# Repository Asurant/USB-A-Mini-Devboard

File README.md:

# USB-A-Mini-Devboard
This is a small USB A Devboard I made. It uses a CH32V003J4M6 as the MCU. It was has 8 pins, 2 for the VBUS, 2 for the GND, and 4 for sensors and similar items. It is 34.5mm in length and 17mm in width.

## Hardware

[KiCanvas Link](https://kicanvas.org/?repo=https%3A%2F%2Fgithub.com%2FAsurant%2FUSB-A-Mini-Devboard%2Ftree%2Fmain%2Fsrc%2Fkicad)
### Schematic

### PCB

### Case

I personally hate it when 3D prints need outside items to make them work so I designed this case not to require screws but instead inbuilt pegs.

### Render

[Onshape Link](https://cad.onshape.com/documents/5c65439f048b848584ec4460/w/9e9735b3b4676a2554d27bed/e/21772a49cf2d0c4a67fcd84c?renderMode=0&uiState=6a110efd986242b2ed622441)

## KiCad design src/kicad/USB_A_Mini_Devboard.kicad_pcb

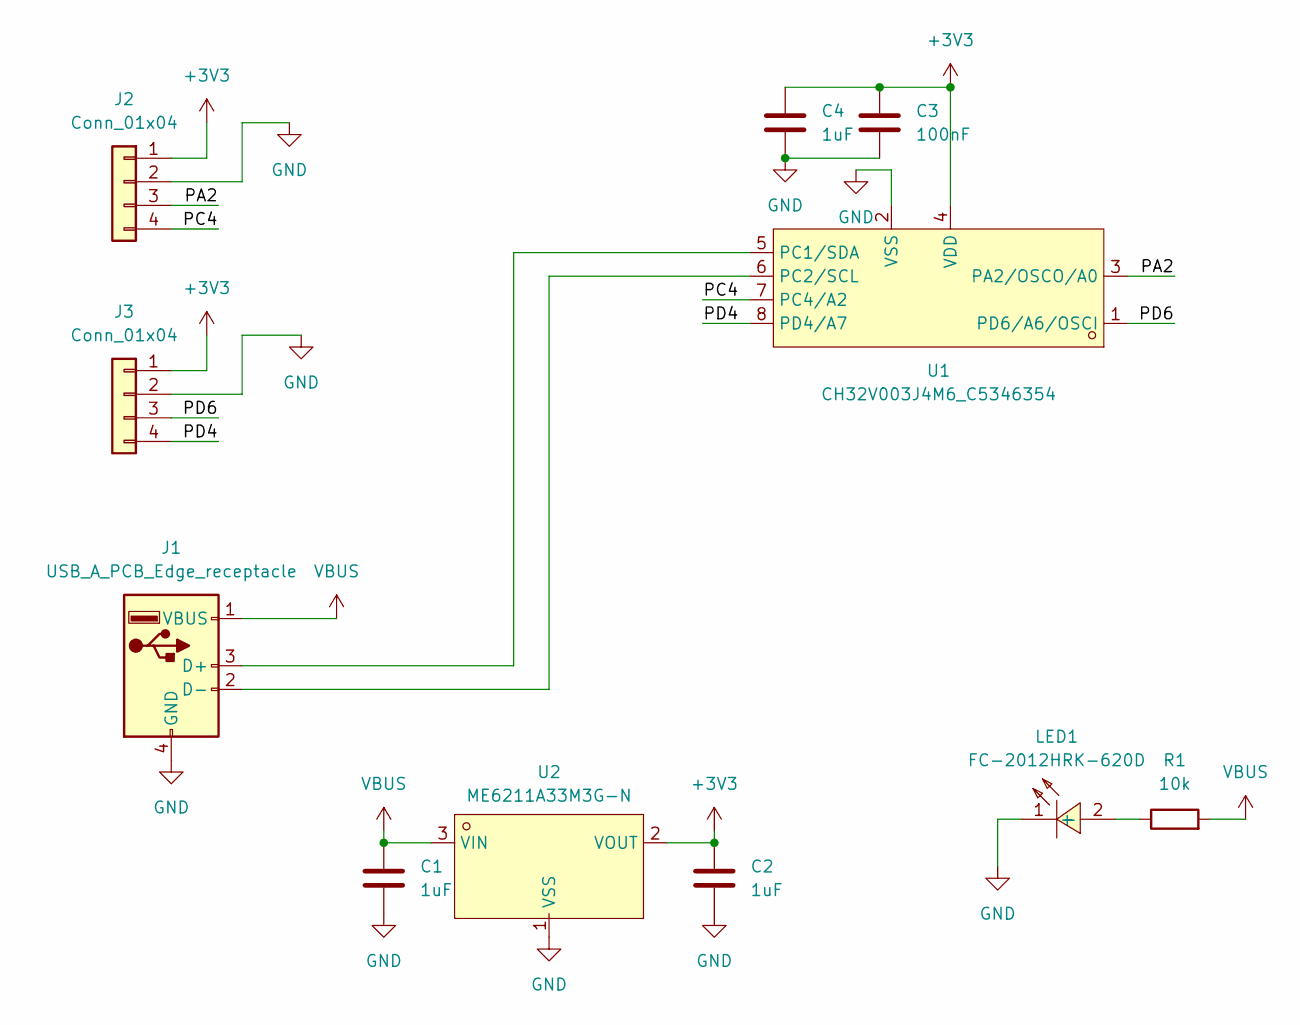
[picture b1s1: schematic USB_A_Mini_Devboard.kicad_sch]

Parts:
C1, C2, C4: 1uF; C_0603_1608Metric; LCSC Part C29936
C3: 100nF; C_0603_1608Metric; LCSC Part C1591
J1: USB_A_PCB_Edge_receptacle
J2, J3: Conn_01x04; PinHeader_1x04_P2.54mm_Vertical; LCSC Part C2691448
LED1: FC-2012HRK-620D; LED0805-RD; MPN NCD0805R1; LCSC Part C84256
R1: 10k; R_0603_1608Metric; LCSC Part C2930027
U1: CH32V003J4M6_C5346354; SOP-8_L4.9-W3.8-P1.27-LS6.0-BL; MPN CH32V003J4M6; LCSC Part C5346354
U2: ME6211A33M3G-N; SOT-23-3_L2.9-W1.6-P1.90-LS2.8-BR; MPN ME6211A33M3G-N; LCSC Part C168807

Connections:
+3V3: C2.1, C3.1, C4.1, J2.1, J3.1, U1.4 (VDD), U2.2 (VOUT)
/PA2: J2.3, U1.3 (PA2/OSCO/A0)
/PC4: J2.4, U1.7 (PC4/A2)
/PD4: J3.4, U1.8 (PD4/A7)
/PD6: J3.3, U1.1 (PD6/A6/OSCI)
GND: C1.2, C2.2, C3.2, C4.2, J1.4 (GND), J2.2, J3.2, LED1.1 (-), U1.2 (VSS), U2.1 (VSS)
unnamed: J1.3 (D+), U1.5 (PC1/SDA)
unnamed: J1.2 (D-), U1.6 (PC2/SCL)
unnamed: LED1.2 (+), R1.1
VBUS: C1.1, J1.1 (VBUS), R1.2, U2.3 (VIN)

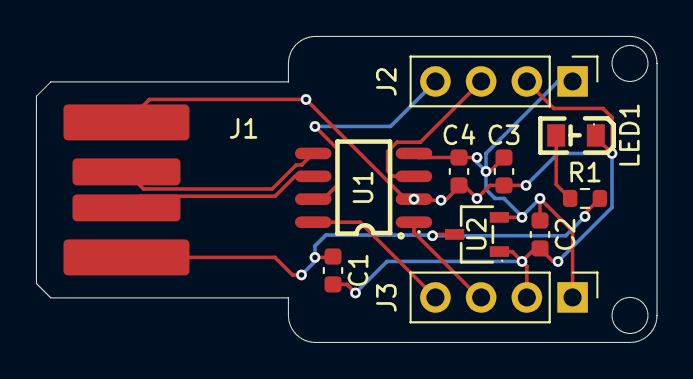
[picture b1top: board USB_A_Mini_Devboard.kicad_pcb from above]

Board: 2 copper layers, 34.5 x 17.0 mm, 11 parts (0 on the bottom side), 10 nets.

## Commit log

2026-05-19 Rename Screenshot 2026-05-19 121321.png to Image8
2026-05-19 Rename Image8 to Image8.png
2026-05-19 Rename Screenshot 2026-05-19 121354.png to Image9.png
2026-05-19 Rename Screenshot 2026-05-19 121423.png to Image10.png
2026-05-23 Rename src/kicad/USB_A_Mini_Devboard.step to src/USB_A_Mini_Devboard.step
